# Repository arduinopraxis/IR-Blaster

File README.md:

# IR-Blaster

The IR Blaster is a simple IR sender module with an onbloard ESP8266 microcontroller board.
You can controll RGB LED stripes or a TV with the IR Blaster and a smartphone or tablet.

This smartphone project is published in my Book "Heimautomation mit Arduino, ESP8266 und Raspberry Pi, ISBN: 9783958456716"
https://www.mitp.de/IT-WEB/Elektronik-Maker/Heimautomation-mit-Arduino-ESP8266-und-Raspberry-Pi.html

## Application
Application with webinterface via Node-RED

## Microcontroller
Wemos D1 Mini

## Circuit Diagram

## PCB

## Firmware Wemos D1 Mini
tasmota-sensors.bin 
see https://github.com/arendst/Tasmota/releases/

## BOM
- 1 PCB (IR Blaster Maxi Wemos, Rev.A)
- 2 Headers 1x8pin (for Wemos D1 Mini)
- 7 Transistor BC846 SMD (T1 - T7)
- 7 Resistor SMD 1206 100 R (R4, R5, R6, R10, R11, R12, R13)
- 7 Resistor SMD 1206 1k (R1, R2, R3, R7, R8, R9, R14)
- 7 IR LED TSUS 5400 TEL 950nm (LED1 - LED7)

## Case 3D Print
see https://www.thingiverse.com/thing:2412098

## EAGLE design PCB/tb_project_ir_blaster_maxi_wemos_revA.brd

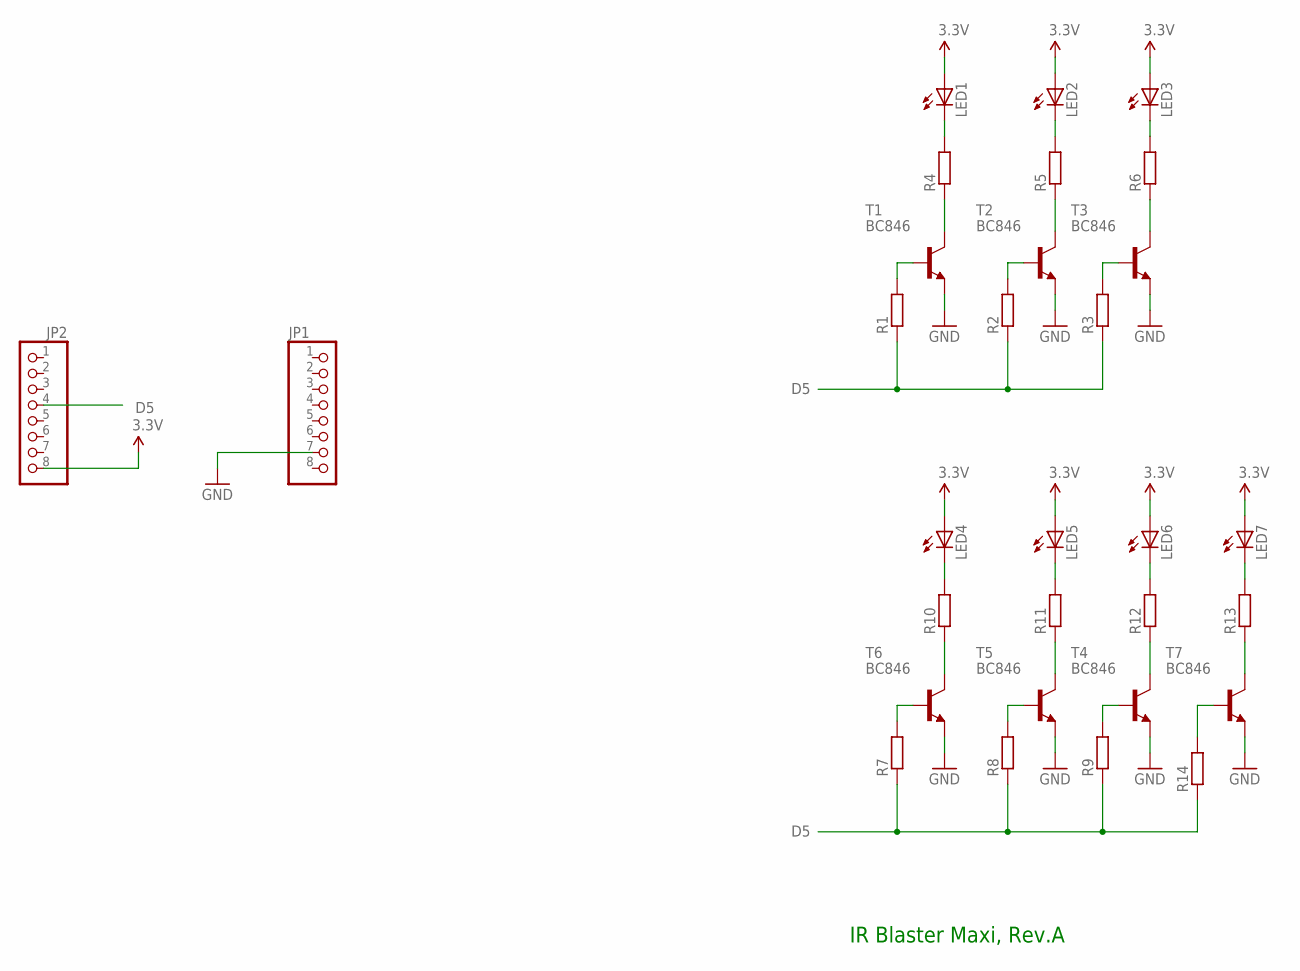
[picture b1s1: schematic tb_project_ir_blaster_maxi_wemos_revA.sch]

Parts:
JP1, JP2: PINHD-1X8; 1X08
LED1, LED2, LED3, LED4, LED5, LED6, LED7: LED5MM
R1, R2, R3, R4, R5, R6, R7, R8, R9, R10, R11, R12, R13, R14: R-EU_R1206; R1206
T1, T2, T3, T4, T5, T6, T7: BC846; SOT23

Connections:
3.3V: JP2.8, LED1.A, LED2.A, LED3.A, LED4.A, LED5.A, LED6.A, LED7.A
D5: JP2.4, R1.1, R2.1, R3.1, R7.1, R8.1, R9.1, R14.1
GND: JP1.7, T1.2 (E), T2.2 (E), T3.2 (E), T4.2 (E), T5.2 (E), T6.2 (E), T7.2 (E)
unnamed: LED4.K (C), R10.2
unnamed: LED1.K (C), R4.2
unnamed: LED2.K (C), R5.2
unnamed: LED3.K (C), R6.2
unnamed: R4.1, T1.3 (C)
unnamed: R5.1, T2.3 (C)
unnamed: R6.1, T3.3 (C)
unnamed: R1.2, T1.1 (B)
unnamed: R2.2, T2.1 (B)
unnamed: R3.2, T3.1 (B)
unnamed: LED5.K (C), R11.2
unnamed: LED6.K (C), R12.2
unnamed: R10.1, T6.3 (C)
unnamed: R11.1, T5.3 (C)
unnamed: R12.1, T4.3 (C)
unnamed: R7.2, T6.1 (B)
unnamed: R8.2, T5.1 (B)
unnamed: R9.2, T4.1 (B)
unnamed: LED7.K (C), R13.2
unnamed: R13.1, T7.3 (C)
unnamed: R14.2, T7.1 (B)

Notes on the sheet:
IR Blaster Maxi, Rev.A

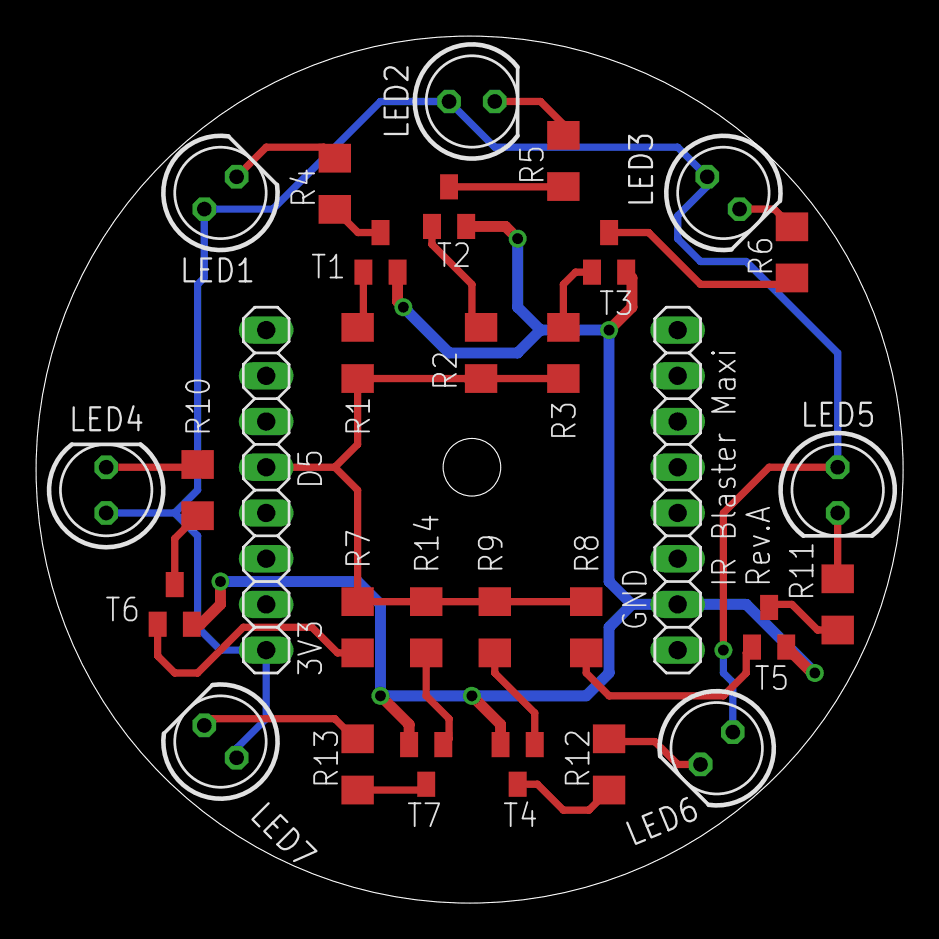
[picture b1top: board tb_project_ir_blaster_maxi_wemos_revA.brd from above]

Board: 2 copper layers, 48.2 x 48.2 mm, 30 parts (0 on the bottom side), 24 nets.

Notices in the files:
parts and their libraries:
freetronics-original: Licensing: CC v3.0 Share-Alike You are welcome to use this library for commercial purposes.
